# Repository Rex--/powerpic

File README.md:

# PowerPIC Calculator Watch
The PowerPIC is a replacement board for Casio CA-53W Databank watches with
upgraded hardware and customizable firmware. The project was designed with
the intent for a personal watch, but all of the needed design files and
firmware is available for free so anyone can make their own (if you can get
the PICs!).

## Features
- Full control of all 82 segments on the original display.
- Interrupt enabled keypad and buttons.
- Variable frequency piezo buzzer.
- Single color LED backlight.
- Built in temperature sensor.
- 12-bit ADC for sensing battery charge.

## Documentation
**Firmware:** The current state of the firmware is heavily evolving, so
the best source of documentation is the code itself, located in the `firmware/`
directory. A Doxyfile is provided, however the generated documentation should
be considered incorrect and outdated.

**Hardware:** Design files and schematics are available in the `hardware/`
directory.

## Credits
Thanks to Travis and Joey, I obtained a lot of inspiration from their projects:
- [GoodWatch](https://github.com/travisgoodspeed/goodwatch) --
Another CA-53W replacement board based on TI's MSP430.
- [Sensor Watch](https://github.com/joeycastillo/Sensor-Watch) --
A replacement board for the classic Casio F-91W based on Microchip's ATSAML22.

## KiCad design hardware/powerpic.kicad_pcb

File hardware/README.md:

# PowerPIC Hardware

The PowerPIC is built on a PIC16LF19197 with 56KB of flash memory and 4KB of RAM.
Required features included: a real time clock and calendar module for timekeeping,
a LCD controller for driving the stock Casio display, and a 10-bit PWM for driving
the piezoelectric buzzer. Some additional useful features are: a 12-bit ADC for roughly
determining battery level, and a temperature sensor for roughly gauging temperature.

## Bill of Materials

The bill of materials changes from board to board, even among versions, based on different LEDs/Crystals.
Care should be taken to match the associated passives with each component.

| Ref | Value | Footprint |
|-----|-------|:----------|
| C1, C2 | 0.1μF | 0402 |
| C3, C4 | | 0603 |
| C5, C6, C7 | 0.27μF | 0402 |
| C8 | 1μF | 0402 |
| D1 | | 0402 |
| D2 | CFSH05-20L | SOD-882 |
| R1 | | 0603 |
| R2 | 680Ω | 0402 |
| U1 | PIC16LF19197-x/MR | QFN-64 |
| Y1 | 32.768kHz | 2-3.2x1.5 |

**C3, C4** - These capacitors should be chosen based upon the crystal. \
**D1** - Most 0402 LEDs should work. Maximum height is unknown, just keep it thin. I've found that diffused R/A LEDs work well, such as `LT VH9G` \
**R1** - Based upon the forward voltage of the chosen LED. Should keep max current under 2mA, preferably 1mA.

## Changelog

**Version 3.0**
- Switch to 4 layer PCB.
- Add charging circuit for ML2016 batteries.

**Version 2.1**
- Added POGO pin for buzzer + to replace the spring.
- Added POGO pin for buzzer - to replace ground tab.

**Version 2.0**
- Added experimental backlight.
- Added RTC crystal for accurate timekeeping.

**Version 1.1**
- Switched buzzer from RF0 to RG7 so we can use the PWM peripheral.
- Switched keypad rows to RA0-RA3. Row 1 was using RA5 which is VBAT and unusable as digital output
- Added additional test points for the side buttons, allowing buttons to be simulated for development
- Added additional GND test point

**Version 1.0**
 - First hardware version

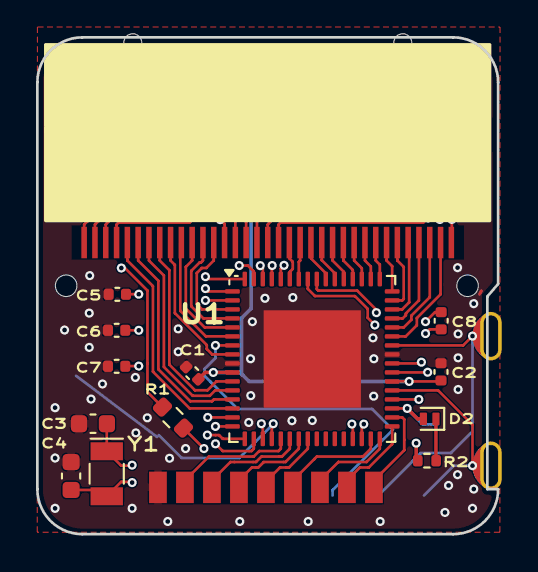
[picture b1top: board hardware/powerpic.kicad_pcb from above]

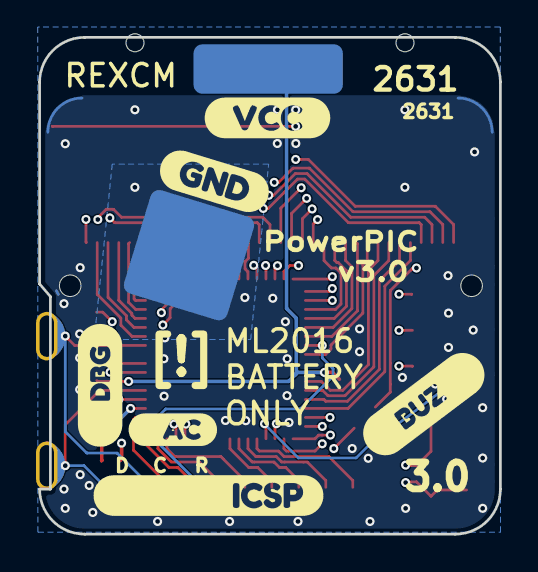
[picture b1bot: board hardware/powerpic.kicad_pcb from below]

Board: 4 copper layers, 25.6 x 27.6 mm, 21 parts (6 on the bottom side), 60 nets.

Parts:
C1, C2: 0.1μF; C_0402_1005Metric
C3, C4: TBD; C_0603_1608Metric
C5, C6, C7: 0.27μF; C_0402_1005Metric
C8: 1μF; C_0402_1005Metric
D1: LCD_LED; LED_0402_1005Metric
D2: D_Filled; D_SOD-882
PPC1: ppc-board
R1: TBD; R_0603_1608Metric
R2: 600; R_0402_1005Metric
U1: PIC16LF1919x-I/MR; QFN-64-1EP_9x9mm_P0.5mm_EP5.4x5.4mm
Y1: 32.768kHz; Crystal_SMD_MicroCrystal_CC7V-T1A-2Pin_3.2x1.5mm
kibuzzard-6619F1C8: G***; kibuzzard-6619F1C8
kibuzzard-6619F3FA: G***; kibuzzard-6619F3FA
kibuzzard-6619F6E4: G***; kibuzzard-6619F6E4
kibuzzard-6619F45C: G***; kibuzzard-6619F45C
kibuzzard-6619F370: G***; kibuzzard-6619F370
kibuzzard-6619F682: G***; kibuzzard-6619F682

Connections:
/ADJ: PPC1.5 (ADJ), PPC1.52 (DAT), U1.37 (RB7/SEG39/ICSPDAT)
/BUZZ: PPC1.3 (buzz_p), U1.20 (COM6/RG6)
/CASE: D2.2 (A), PPC1.53 (DBG), U1.35 (RC4/SEG16)
/CFLY1: C8.1, U1.57 (CFLY1/SEG32/RH2)
/CFLY2: C8.2, U1.56 (CFLY2/SEG40/RH3)
/COL0: PPC1.11 (COL0), U1.31 (RC6/SEG27)
/COL1: PPC1.12 (COL1), U1.32 (RC7/SEG28)
/COL2: PPC1.13 (COL2), U1.33 (RC2/SEG13)
/COL3: PPC1.14 (COL3), U1.34 (RC3/SEG17)
/COM0: PPC1.15 (COM0), U1.63 (COM0/RE3)
/COM1: PPC1.16 (COM1), U1.62 (COM1/RE4)
/COM2: PPC1.17 (COM2), U1.61 (COM2/RE5)
/COM3: PPC1.18 (COM3), U1.60 (COM3/RE6)
/LIGHT: R1.2, U1.19 (COM7/SEG15/RG7)
/MODE: PPC1.4 (MODE), PPC1.51 (CLK), U1.42 (RB6/SEG38/ICSPCLK)
/ROW0: PPC1.10 (ROW0), U1.24 (RA0/SEG33)
/ROW1: PPC1.9 (ROW1), U1.23 (RA1/SEG18)
/ROW2: PPC1.8 (ROW2), U1.22 (RA2/SEG34)
/ROW3: PPC1.7 (ROW3), U1.21 (RA3/SEG35)
/SEG0: PPC1.19 (SEG0), U1.14 (SEG22/RF4)
/SEG1: PPC1.20 (SEG1), U1.13 (SEG23/RF5)
/SEG2: PPC1.21 (SEG2), U1.12 (SEG24/RF6)
/SEG3: PPC1.22 (SEG3), U1.11 (SEG25/RF7)
/SEG4: PPC1.23 (SEG4), U1.8 (SEG26/RG4)
/SEG5: PPC1.24 (SEG5), U1.6 (SEG45/RG3)
/SEG6: PPC1.25 (SEG6), U1.5 (SEG44/RG2)
/SEG7: PPC1.26 (SEG7), U1.4 (SEG43/RG1)
/SEG8: PPC1.27 (SEG8), U1.3 (SEG42/RG0)
/SEG9: PPC1.28 (SEG9), U1.17 (SEG19/RF1)
/SEG10: PPC1.29 (SEG10), U1.15 (SEG21/RF3)
/SEG11: PPC1.30 (SEG11), U1.16 (SEG20/RF2)
/SEG12: PPC1.31 (SEG12), U1.18 (SEG41/RF0)
/SEG13: PPC1.32 (SEG13), U1.39 (RA7/SEG37)
/SEG14: PPC1.33 (SEG14), U1.40 (RA6/SEG36)
/SEG15: PPC1.34 (SEG15), U1.59 (SEG31/RE7)
/SEG16: PPC1.35 (SEG16), U1.58 (RD0/SEG0)
/SEG17: PPC1.36 (SEG17), U1.55 (RD1/SEG1)
/SEG18: PPC1.37 (SEG18), U1.54 (RD2/SEG2)
/SEG19: PPC1.38 (SEG19), U1.53 (RD3/SEG3)
/SEG20: PPC1.39 (SEG20), U1.52 (RD4/SEG4)
/SEG21: PPC1.40 (SEG21), U1.51 (RD5/SEG5)
/SEG22: PPC1.41 (SEG22), U1.50 (RD6/SEG6)
/SEG23: PPC1.42 (SEG23), U1.49 (RD7/SEG7)
/SEG24: PPC1.43 (SEG24), U1.48 (RB0/SEG30)
/SEG25: PPC1.44 (SEG25), U1.47 (RB1/SEG8)
/SEG26: PPC1.45 (SEG26), U1.46 (RB2/SEG9)
/SEG27: PPC1.46 (SEG27), U1.45 (RB3/SEG10)
/SEG28: PPC1.47 (SEG28), U1.44 (RB4/SEG11)
/SEG29: PPC1.48 (SEG29), U1.43 (RB5/SEG29)
/SEG30: PPC1.49 (SEG30), U1.36 (RC5/SEG12)
/SOSCI: C3.1, U1.29 (RC1), Y1.1
/SOSCO: C4.1, U1.30 (RC0), Y1.2
/VLCD1: C7.1, U1.2 (VLCD1/RE0)
/VLCD2: C6.1, U1.1 (VLCD2/RE1)
/VLCD3: C5.1, U1.64 (VLCD3)
/~MCLR: PPC1.50 (~MCLR), U1.7 (VPP/~MCLR/RG5)
GND: C1.1, C2.1, C3.2, C4.2, C5.2, C6.2, C7.2, D1.1 (K), PPC1.2 (GND), PPC1.6 (NC), U1.9 (VSS), U1.41 (VSS), U1.65 (VSS)
unnamed: D1.2 (A), R1.1
unnamed: D2.1 (K), R2.1
VCC: C1.2, C2.2, PPC1.1 (VCC), R2.2, U1.10 (VDD), U1.38 (VDD)

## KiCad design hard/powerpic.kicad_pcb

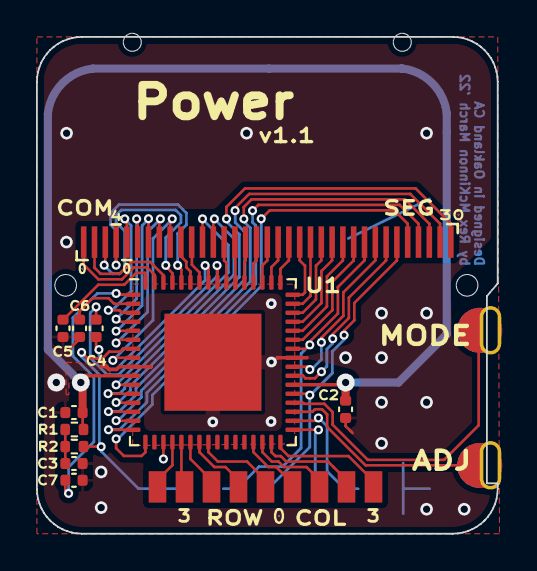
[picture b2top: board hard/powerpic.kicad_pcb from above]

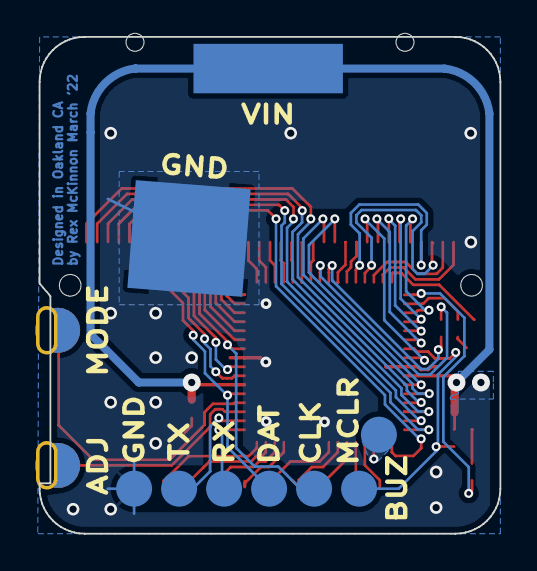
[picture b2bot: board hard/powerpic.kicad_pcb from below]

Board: 2 copper layers, 25.6 x 27.6 mm, 17 parts (6 on the bottom side), 58 nets.

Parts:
C1, C2: 0.1μF; C_0402_1005Metric
C3: 10nF; C_0402_1005Metric
C4: 1μF; C_0402_1005Metric
C5, C6: 0.27μF; C_0402_1005Metric
C7: NC; C_0402_1005Metric
GND: Progo_Pad_D2.0mm
PPC1: ppc-board
R1, R2: 100Ω; R_0402_1005Metric
TP1: ~{MCLR}; Progo_Pad_D2.0mm
TP2: ICSP_CLK; Progo_Pad_D2.0mm
TP3: ICSP_DAT; Progo_Pad_D2.0mm
TP4: UART_RX; Progo_Pad_D2.0mm
TP5: UART_TX; Progo_Pad_D2.0mm
U1: PIC16LF1919x-I/MR; QFN-64-1EP_9x9mm_P0.5mm_EP5.4x5.4mm

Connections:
/ADJ: PPC1.5 (ADJ), U1.35 (RC4/SEG16)
/BUZZ: PPC1.3 (BUZZ), U1.19 (COM7/SEG15/RG7)
/CFLY1: C4.1, U1.57 (CFLY1/SEG32/RH2)
/CFLY2: C4.2, U1.56 (CFLY2/SEG40/RH3)
/COL0: PPC1.11 (COL0), U1.29 (RC1)
/COL1: PPC1.12 (COL1), U1.30 (RC0)
/COL2: PPC1.13 (COL2), U1.31 (RC6/SEG27)
/COL3: PPC1.14 (COL3), U1.32 (RC7/SEG28)
/COM0: PPC1.15 (COM0), U1.63 (COM0/RE3)
/COM1: PPC1.16 (COM1), U1.62 (COM1/RE4)
/COM2: PPC1.17 (COM2), U1.61 (COM2/RE5)
/COM3: PPC1.18 (COM3), U1.60 (COM3/RE6)
/KTEST: PPC1.6 (NC), U1.20 (COM6/RG6)
/MODE: PPC1.4 (MODE), U1.36 (RC5/SEG12)
/ROW0: PPC1.10 (ROW0), U1.24 (RA0/SEG33)
/ROW1: PPC1.9 (ROW1), U1.23 (RA1/SEG18)
/ROW2: PPC1.8 (ROW2), U1.22 (RA2/SEG34)
/ROW3: PPC1.7 (ROW3), U1.21 (RA3/SEG35)
/SEG0: PPC1.19 (SEG0), U1.3 (SEG42/RG0)
/SEG1: PPC1.20 (SEG1), U1.4 (SEG43/RG1)
/SEG2: PPC1.21 (SEG2), U1.5 (SEG44/RG2)
/SEG3: PPC1.22 (SEG3), U1.6 (SEG45/RG3)
/SEG4: PPC1.23 (SEG4), U1.8 (SEG26/RG4)
/SEG5: PPC1.24 (SEG5), U1.59 (SEG31/RE7)
/SEG6: PPC1.25 (SEG6), U1.58 (RD0/SEG0)
/SEG7: PPC1.26 (SEG7), U1.11 (SEG25/RF7)
/SEG8: PPC1.27 (SEG8), U1.12 (SEG24/RF6)
/SEG9: PPC1.28 (SEG9), U1.55 (RD1/SEG1)
/SEG10: PPC1.29 (SEG10), U1.54 (RD2/SEG2)
/SEG11: PPC1.30 (SEG11), U1.53 (RD3/SEG3)
/SEG12: PPC1.31 (SEG12), U1.52 (RD4/SEG4)
/SEG13: PPC1.32 (SEG13), U1.51 (RD5/SEG5)
/SEG14: PPC1.33 (SEG14), U1.50 (RD6/SEG6)
/SEG15: PPC1.34 (SEG15), U1.49 (RD7/SEG7)
/SEG16: PPC1.35 (SEG16), U1.48 (RB0/SEG30)
/SEG17: PPC1.36 (SEG17), U1.47 (RB1/SEG8)
/SEG18: PPC1.37 (SEG18), U1.46 (RB2/SEG9)
/SEG19: PPC1.38 (SEG19), U1.45 (RB3/SEG10)
/SEG20: PPC1.39 (SEG20), U1.44 (RB4/SEG11)
/SEG21: PPC1.40 (SEG21), U1.43 (RB5/SEG29)
/SEG22: PPC1.41 (SEG22), TP2.1, U1.42 (RB6/SEG38/ICSPCLK)
/SEG23: PPC1.42 (SEG23), U1.40 (RA6/SEG36)
/SEG24: PPC1.43 (SEG24), U1.39 (RA7/SEG37)
/SEG25: PPC1.44 (SEG25), TP3.1, U1.37 (RB7/SEG39/ICSPDAT)
/SEG26: PPC1.45 (SEG26), U1.17 (SEG19/RF1)
/SEG27: PPC1.46 (SEG27), U1.16 (SEG20/RF2)
/SEG28: PPC1.47 (SEG28), U1.15 (SEG21/RF3)
/SEG29: PPC1.48 (SEG29), U1.14 (SEG22/RF4)
/SEG30: PPC1.49 (SEG30), U1.13 (SEG23/RF5)
/UART_RX: TP4.1, U1.33 (RC2/SEG13)
/UART_TX: TP5.1, U1.34 (RC3/SEG17)
/VLCD1: C6.1, U1.2 (VLCD1/RE0)
/VLCD2: C7.1, U1.1 (VLCD2/RE1)
/VLCD3: C5.1, U1.64 (VLCD3)
/~MCLR: R2.2, TP1.1, U1.7 (VPP/~MCLR/RG5)
GND: C1.1, C2.1, C3.1, C5.2, C6.2, C7.2, GND.1, PPC1.2 (GND), U1.9 (VSS), U1.41 (VSS), U1.65 (VSS)
unnamed: C3.2, R1.1, R2.1
VCC: C1.2, C2.2, PPC1.1 (VCC), R1.2, U1.10 (VDD), U1.38 (VDD)

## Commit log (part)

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2022-02-08 Added powerpic schematic
2022-02-10 Added PCB design files
2022-02-10 Added some silkscreen labels, and noticed a design error. Final commit before version bump
2022-03-05 Version 1.0 of pcb
2022-03-05 Version 1.1 Release
2022-03-05 Changed directory naming scheme
2022-03-11 Basic firmware layout, included UART driver as example.
2022-03-11 Changed some links in the READMEs
2022-03-11 Fixed a link to my website
2022-05-04 Initial firmware commit- implements basic watch functionalty using smaller 'mode' applications.
2022-05-05 Added configurable fonts for modes.
2022-05-12 Redesigned board with RTCXTAL and led backlight
2022-05-12 Cleaned root readme
2022-05-21 Added support for v2 boards. Lots of various other changes
2022-05-23 Changed clock speed to 32MHz from 1MHz. Split EUSART configuration for UART into a driver.
2022-05-30 Re-work inevitable
2022-06-02 Empty Slate, Fresh Canvas.
2022-06-21 Re-write of the core system completed.
2022-06-22 Added a big, ugly hacki of an alarm library.
2022-06-23 Display driver now less aggressive about positions when displaying numbers.
2022-06-23 Added alarmclock mode that mimcs a stock casio.
2022-06-23 Alarmclock is now almost exactly the same as stock casio.
2022-06-23 Mode's run function now returns value signalling to switch modes.
2022-06-23 Added simple daemon functionality for mode's to optionally implement.
2022-06-23 Added a way to remove alarms with their event data.
2022-06-24 Fixed a bug in alarm lib where the number of registered alarms wasnt getting decremented when one was deleted.
2022-06-24 Added alarmclock daemon that beeps on hourly and daily alarm events.
2022-06-29 Fixed tick lib to generate an event at the requested rate. Previously, every event was resetting the tick timer.
2022-06-30 Completely changed the way mode application are configured. Mode applications now configure libraries by calling the library's functions.
2022-06-30 Changed programmer baudrate to be configurable in the Makefile.
2022-06-30 Added super barebones clock mode application.
2022-06-30 Changed the main loop to sleep after executing all events.
2022-07-19 Added more information to READMEs
2022-07-24 clock_mode: Fixed a bug where the hour tens digit was not getting cleared.
2022-07-25 display library: Fixed a bug when clearing the entire secondary display.
2022-07-25 clock_mode: - Added date display with '/' (divide) key. - Date is now settable by the user in the ADJ button menu.
2022-07-26 alarm mode: Improved hourly chime sound and duration.
2022-07-26 clock mode: Changed the way 24HR time is converted. Should fix bug where 2000-2100 were not displaying correctly in 12HR mode.
2022-08-07 buzzer lib: Work on changing buzzer timer to be interrupt-based.
2022-08-07 pwm driver: Fixed a mismatched return type. backlight lib: Fixed a bug with toggling the backlight. test mode: Started working towards a 'POST' mode that verifies watch functionality.
2022-08-07 display lib: Added function to display specific segments. This allows custom characters to easily be drawn.
2022-08-07 clock mode: Added better looking weekday display
2022-08-08 Added new POST procedure to run after reset.
2022-08-09 Updated readmes and added a header photo.
2022-08-09 Added legacy v1.0 schematic.
2022-08-09 display lib: Fixed a bug where all segments on the secondary display were not getting cleared.
2022-08-09 Changed plain text block to quote.
2022-08-13 battery lib: Now enabling ADC only when sampling.
2022-08-13 mode lib: All mode functions now optional except start.
2022-08-13 power mode: Added new mode that displays battery voltage.
2022-08-13 display lib: Split library into multiple files. Each display group has its own file. This hopefully will allow for easier expansion of the lib.
2022-08-13 firmware readme: Updated note about compiler version.
2022-08-14 clock, alarmclock, power modes: Better interfaces.
2022-08-17 display lib: Polished display_primary_number. Now accepts negative positions. Now accepts negative numbers. Verifies number is in range, and displays error if not.
2022-08-17 settings mode: Added basic mode to edit system settings.
2022-08-18 Starting work on version 3 of the hardware.
2022-08-19 hardware: Minor changes. Mostly playing around in the new kicad nightly.
2022-08-19 temperature mode: Calculate temperature based on internal sensor.
2022-08-19 thermometer mode: Basic mode that displays the temperature. The temperature lib it's based on uses the internal temp sensor so it is labeled CPU to indicate it's probably not ambient temp.
2022-08-20 settings lib: Basic data storage lib. Uses device EEPROM.
2022-08-20 mode settings: Added persistent settings to clock and settings modes.
2022-08-26 Switched firmware to use flipflop bootloader.
2022-10-06 display lib: Added functions to display hex numbers.
2022-10-06 No longer using bootloader. No good way to start bootloader yet.
2022-10-15 clock mode: Added backlight button to clock face.
2022-10-15 firmware main: Changed the initial date.
2022-10-15 thermometer mode: Added calibrate functionality. temperature lib: Added calibrate procedure that records the current adc reading. nvm driver: Added procedure to read from all PFM locations.
2022-10-17 Makefile: Now uses .d files to compile based on changes
2022-10-31 buzzer lib: Added ability to play RTTTL ringtones. Currently these ringtones are stored as strings in RTTTL format.
2022-12-12 Fixed an issue when compiling from scratch. I believe this is due to an issue in the `-include` directive in Make 4.4. Depends list is now generated based on existing files.
2023-01-28 buttons lib: Added some basic debouncing using timer1.
2023-02-03 pwm driver: switch PWM4 to TMR4. The PWM4 peripheral used for buzzer now uses Timer4 instead of Timer2.
2023-02-04 stopwatch mode: Work towards adding a stopwatch mode that implements various timers.
2023-02-04 Added countdown mode
2023-02-04 Added super basic timer mode, only countdown is implemented
2023-04-07 Increased buffer to 64 bytes and changed default baudrate to 9600.
2023-04-07 Added basic debug display. The primary display is printed out as ascii characters. Currently only enabled on INFO and higher log levels.
2023-06-30 settings lib: expanded integer settings.
2023-12-10 Small changes to compile with version 2.45 of xc8: - putch function changed to take just "char" as argument. - Configuration bit for PowerUp Timer selection changed from PWRTE to PWRTS.
2023-12-10 Fixed warnings in timer.c
2023-12-14 Modified clock mode to hopefully be more efficient: - EEPROM setting get loaded on every start of the mode, instead of once at init. - Changed method of updating the seconds by incrementing and synci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
2024-02-09 main: logging lib: Added wait loop for TX buffer to empty.
2024-02-09 device_config: flipflop bootloader now uses CONFIG3 - WDT.
2024-02-09 rtcc driver: added chip specific logic to driver
2024-02-09 datetime lib: updated to use new rtcc driver
2024-02-09 alarm lib: Fixed longstading bugs
2024-02-09 alarmclock mode: updated to use new alarm lib
2024-02-09 timer mode: fixed bugs in countdown timer, added mario chime
2024-02-09 uptime mode: Added basicc uptime mode that counts days
2024-02-09 settings mode: Changed to generic bytes with ids for settings
2024-02-09 mode config: Changed mode order, added uptime setting.
2024-02-09 main: removed setting of default date
2024-04-11 clock mode: sync with seconds upon starting the mode
2024-04-13 makefile: flattened build directory tree
2024-04-27 release version 2.1
2024-04-27 Readme: updated docs and license year
2024-04-27 change name to CasiOS
2024-04-27 makefile: build firmware based on list of modes
2025-04-19 libs: add initialization log for each lib
2025-04-19 buzzer lib: register isr only when needed
2025-04-19 uptime mode: fixed error in alarm set function call
2025-04-19 keypad driver: make keypad scanner more robust
2025-04-19 timer mode: add very basic stopwatch functionality
2025-04-19 update mode: add simple mode to reboot the device which allows for firmware updates
